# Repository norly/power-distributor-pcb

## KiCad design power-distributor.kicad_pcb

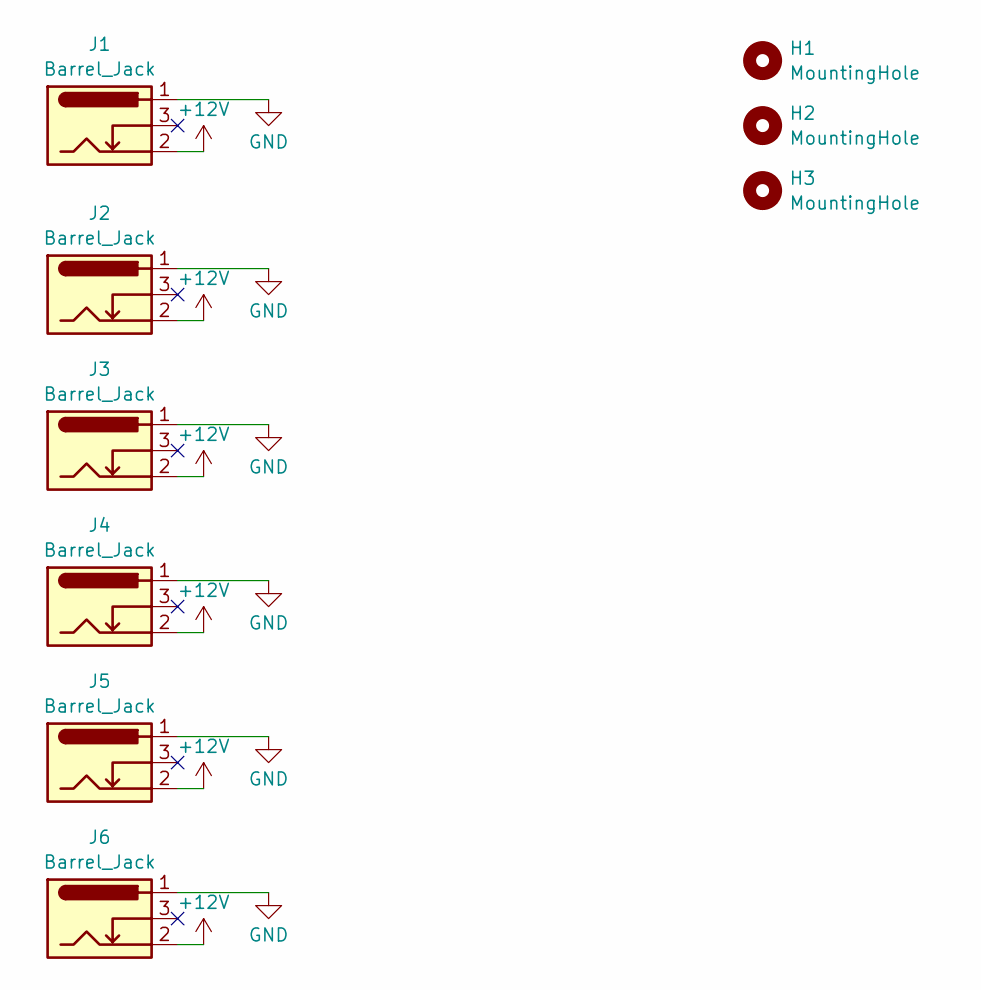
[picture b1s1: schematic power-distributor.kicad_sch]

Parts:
H1, H2, H3: MountingHole; MountingHole_2.7mm_M2.5
J1, J2, J3, J4, J5, J6: Barrel_Jack; BarrelJack_Horizontal

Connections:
+12V: J1.2, J2.2, J3.2, J4.2, J5.2, J6.2
GND: J1.1, J2.1, J3.1, J4.1, J5.1, J6.1

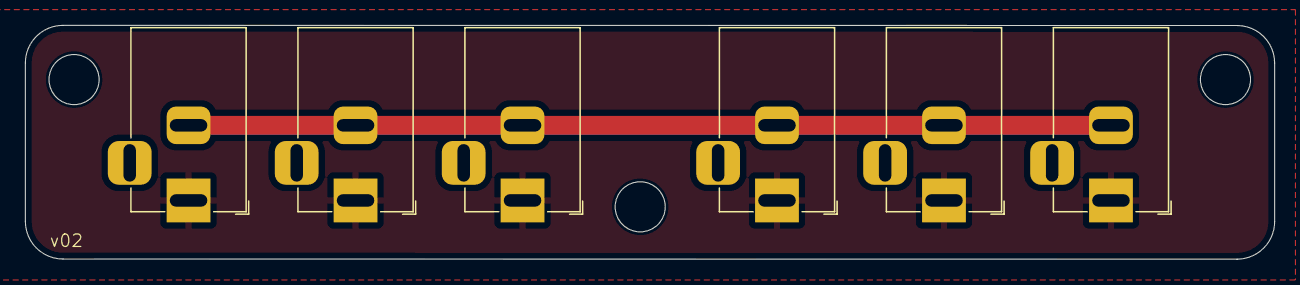
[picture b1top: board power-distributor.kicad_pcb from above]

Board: 2 copper layers, 99.8 x 18.7 mm, 9 parts (0 on the bottom side), 2 nets.

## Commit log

2024-09-07 Add .gitignore
2024-09-07 v01: Initial version
2024-09-08 LICENSE: CC0
2024-10-03 v02: Bigger mounting holes, more even spacing
